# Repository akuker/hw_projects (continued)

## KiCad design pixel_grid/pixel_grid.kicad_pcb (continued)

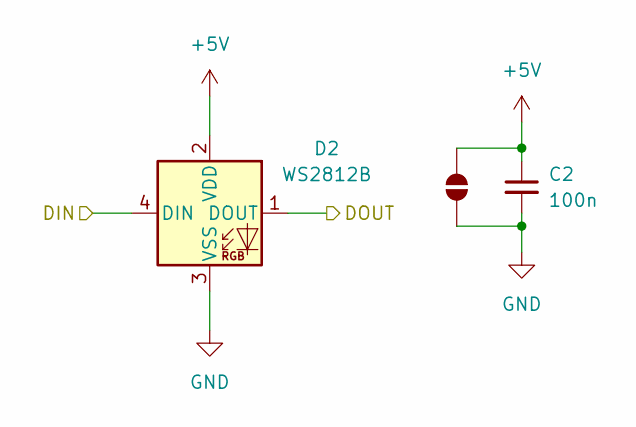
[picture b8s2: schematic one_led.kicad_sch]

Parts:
C2: 100n; C_0402_1005Metric; LCSC C1525
D2: WS2812B; LED_WS2812B-1615_1.5x1.6mm; LCSC C5349954
JP71: SolderJumper_2_Open; Pin_D0.6mm_Via

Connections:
+5V: C2.1, D2.2 (VDD), JP71.2 (B); also elsewhere on the board
/Ten_Leds/One_LED1/DOUT: D2.1 (DOUT); also elsewhere on the board
/Ten_Leds/One_LED/DOUT: D2.4 (DIN); also elsewhere on the board
GND: C2.2, D2.3 (VSS), JP71.1 (A); also elsewhere on the board

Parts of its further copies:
C1, C3, C4, C5, C6, C7, C8, C9, C10, C11, C12, C13, C14, C15, C16, C17, C18, C19, C20, C21, C22, C23, C24, C25, C26, C27, C28, C29, C30, C31, C32, C33, C34, C35, C36, C37, C38, C39, C40, C41, C42, C43, C44, C45, C46, C47, C48, C49, C50, C51, C52, C53, C54, C55, C56, C57, C58, C59, C60, C61, C62, C63, C64, C65, C66, C67, C68, C69, C70, C71, C72, C73, C74, C75, C76, C77, C78, C79, C80, C81, C82, C83, C84, C85, C86, C87, C88, C89, C90, C91, C92, C93, C94, C95, C96, C97, C98, C99, C100: 100n; C_0402_1005Metric; LCSC C1525
D1, D3, D4, D5, D6, D7, D8, D9, D10, D11, D12, D13, D14, D15, D16, D17, D18, D19, D20, D21, D22, D23, D24, D25, D26, D27, D28, D29, D30, D31, D32, D33, D34, D35, D36, D37, D38, D39, D40, D41, D42, D43, D44, D45, D46, D47, D48, D49, D50, D51, D52, D53, D54, D55, D56, D57, D58, D59, D60, D61, D62, D63, D64, D65, D66, D67, D68, D69, D70, D71, D72, D73, D74, D75, D76, D77, D78, D79, D80, D81, D82, D83, D84, D85, D86, D87, D88, D89, D90, D91, D92, D93, D94, D95, D96, D97, D98, D99, D100: WS2812B; LED_WS2812B-1615_1.5x1.6mm; LCSC C5349954
JP1, JP2, JP3, JP4, JP5, JP6, JP7, JP8, JP9, JP10, JP11, JP12, JP13, JP14, JP15, JP16, JP17, JP18, JP19, JP20, JP21, JP22, JP23, JP24, JP25, JP26, JP27, JP28, JP29, JP30, JP31, JP32, JP33, JP34, JP35, JP36, JP37, JP38, JP39, JP40, JP41, JP42, JP43, JP44, JP45, JP46, JP47, JP48, JP49, JP50, JP51, JP52, JP53, JP54, JP55, JP56, JP57, JP58, JP59, JP60, JP61, JP62, JP63, JP64, JP65, JP66, JP67, JP68, JP69, JP70, JP72, JP73, JP74, JP75, JP76, JP77, JP78, JP79, JP80, JP81, JP82, JP83, JP84, JP85, JP86, JP87, JP88, JP89, JP90, JP91, JP92, JP93, JP94, JP95, JP96, JP97, JP98, JP99, JP100: SolderJumper_2_Open; Pin_D0.6mm_Via

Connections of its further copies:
+5V: C1.1, C3.1, C4.1, C5.1, C6.1, C7.1, C8.1, C9.1, C10.1, C11.1, C12.1, C13.1, C14.1, C15.1, C16.1, C17.1, C18.1, C19.1, C20.1, C21.1, C22.1, C23.1, C24.1, C25.1, C26.1, C27.1, C28.1, C29.1, C30.1, C31.1, C32.1, C33.1, C34.1, C35.1, C36.1, C37.1, C38.1, C39.1, C40.1, C41.1, C42.1, C43.1, C44.1, C45.1, C46.1, C47.1, C48.1, C49.1, C50.1, C51.1, C52.1, C53.1, C54.1, C55.1, C56.1, C57.1, C58.1, C59.1, C60.1, C61.1, C62.1, C63.1, C64.1, C65.1, C66.1, C67.1, C68.1, C69.1, C70.1, C71.1, C72.1, C73.1, C74.1, C75.1, C76.1, C77.1, C78.1, C79.1, C80.1, C81.1, C82.1, C83.1, C84.1, C85.1, C86.1, C87.1, C88.1, C89.1, C90.1, C91.1, C92.1, C93.1, C94.1, C95.1, C96.1, C97.1, C98.1, C99.1, C100.1, D1.2 (VDD), D3.2 (VDD), D4.2 (VDD), D5.2 (VDD), D6.2 (VDD), D7.2 (VDD), D8.2 (VDD), D9.2 (VDD), D10.2 (VDD), D11.2 (VDD), D12.2 (VDD), D13.2 (VDD), D14.2 (VDD), D15.2 (VDD), D16.2 (VDD), D17.2 (VDD), D18.2 (VDD), D19.2 (VDD), D20.2 (VDD), D21.2 (VDD), D22.2 (VDD), D23.2 (VDD), D24.2 (VDD), D25.2 (VDD), D26.2 (VDD), D27.2 (VDD), D28.2 (VDD), D29.2 (VDD), D30.2 (VDD), D31.2 (VDD), D32.2 (VDD), D33.2 (VDD), D34.2 (VDD), D35.2 (VDD), D36.2 (VDD), D37.2 (VDD), D38.2 (VDD), D39.2 (VDD), D40.2 (VDD), D41.2 (VDD), D42.2 (VDD), D43.2 (VDD), D44.2 (VDD), D45.2 (VDD), D46.2 (VDD), D47.2 (VDD), D48.2 (VDD), D49.2 (VDD), D50.2 (VDD), D51.2 (VDD), D52.2 (VDD), D53.2 (VDD), D54.2 (VDD), D55.2 (VDD), D56.2 (VDD), D57.2 (VDD), D58.2 (VDD), D59.2 (VDD), D60.2 (VDD), D61.2 (VDD), D62.2 (VDD), D63.2 (VDD), D64.2 (VDD), D65.2 (VDD), D66.2 (VDD), D67.2 (VDD), D68.2 (VDD), D69.2 (VDD), D70.2 (VDD), D71.2 (VDD), D72.2 (VDD), D73.2 (VDD), D74.2 (VDD), D75.2 (VDD), D76.2 (VDD), D77.2 (VDD), D78.2 (VDD), D79.2 (VDD), D80.2 (VDD), D81.2 (VDD), D82.2 (VDD), D83.2 (VDD), D84.2 (VDD), D85.2 (VDD), D86.2 (VDD), D87.2 (VDD), D88.2 (VDD), D89.2 (VDD), D90.2 (VDD), D91.2 (VDD), D92.2 (VDD), D93.2 (VDD), D94.2 (VDD), D95.2 (VDD), D96.2 (VDD), D97.2 (VDD), D98.2 (VDD), D99.2 (VDD), D100.2 (VDD), JP1.2 (B), JP2.2 (B), JP3.2 (B), JP4.2 (B), JP5.2 (B), JP6.2 (B), JP7.2 (B), JP8.2 (B), JP9.2 (B), JP10.2 (B), JP11.2 (B), JP12.2 (B), JP13.2 (B), JP14.2 (B), JP15.2 (B), JP16.2 (B), JP17.2 (B), JP18.2 (B), JP19.2 (B), JP20.2 (B), JP21.2 (B), JP22.2 (B), JP23.2 (B), JP24.2 (B), JP25.2 (B), JP26.2 (B), JP27.2 (B), JP28.2 (B), JP29.2 (B), JP30.2 (B), JP31.2 (B), JP32.2 (B), JP33.2 (B), JP34.2 (B), JP35.2 (B), JP36.2 (B), JP37.2 (B), JP38.2 (B), JP39.2 (B), JP40.2 (B), JP41.2 (B), JP42.2 (B), JP43.2 (B), JP44.2 (B), JP45.2 (B), JP46.2 (B), JP47.2 (B), JP48.2 (B), JP49.2 (B), JP50.2 (B), JP51.2 (B), JP52.2 (B), JP53.2 (B), JP54.2 (B), JP55.2 (B), JP56.2 (B), JP57.2 (B), JP58.2 (B), JP59.2 (B), JP60.2 (B), JP61.2 (B), JP62.2 (B), JP63.2 (B), JP64.2 (B), JP65.2 (B), JP66.2 (B), JP67.2 (B), JP68.2 (B), JP69.2 (B), JP70.2 (B), JP72.2 (B), JP73.2 (B), JP74.2 (B), JP75.2 (B), JP76.2 (B), JP77.2 (B), JP78.2 (B), JP79.2 (B), JP80.2 (B), JP81.2 (B), JP82.2 (B), JP83.2 (B), JP84.2 (B), JP85.2 (B), JP86.2 (B), JP87.2 (B), JP88.2 (B), JP89.2 (B), JP90.2 (B), JP91.2 (B), JP92.2 (B), JP93.2 (B), JP94.2 (B), JP95.2 (B), JP96.2 (B), JP97.2 (B), JP98.2 (B), JP99.2 (B), JP100.2 (B); also elsewhere on the board
/Ten_Leds1/DOUT: D20.1 (DOUT), D21.4 (DIN)
/Ten_Leds1/One_LED1/DOUT: D12.1 (DOUT), D13.4 (DIN)
/Ten_Leds1/One_LED2/DOUT: D13.1 (DOUT), D14.4 (DIN)
/Ten_Leds1/One_LED3/DOUT: D14.1 (DOUT), D15.4 (DIN)
/Ten_Leds1/One_LED4/DOUT: D15.1 (DOUT), D16.4 (DIN)
/Ten_Leds1/One_LED5/DOUT: D16.1 (DOUT), D17.4 (DIN)
/Ten_Leds1/One_LED6/DOUT: D17.1 (DOUT), D18.4 (DIN)
/Ten_Leds1/One_LED7/DOUT: D18.1 (DOUT), D19.4 (DIN)
/Ten_Leds1/One_LED8/DOUT: D19.1 (DOUT), D20.4 (DIN)
/Ten_Leds1/One_LED/DOUT: D11.1 (DOUT), D12.4 (DIN)
/Ten_Leds2/DOUT: D30.1 (DOUT), D31.4 (DIN)
/Ten_Leds2/One_LED1/DOUT: D22.1 (DOUT), D23.4 (DIN)
/Ten_Leds2/One_LED2/DOUT: D23.1 (DOUT), D24.4 (DIN)
/Ten_Leds2/One_LED3/DOUT: D24.1 (DOUT), D25.4 (DIN)
/Ten_Leds2/One_LED4/DOUT: D25.1 (DOUT), D26.4 (DIN)
/Ten_Leds2/One_LED5/DOUT: D26.1 (DOUT), D27.4 (DIN)
/Ten_Leds2/One_LED6/DOUT: D27.1 (DOUT), D28.4 (DIN)
/Ten_Leds2/One_LED7/DOUT: D28.1 (DOUT), D29.4 (DIN)
/Ten_Leds2/One_LED8/DOUT: D29.1 (DOUT), D30.4 (DIN)
/Ten_Leds2/One_LED/DOUT: D21.1 (DOUT), D22.4 (DIN)
/Ten_Leds3/DOUT: D40.1 (DOUT), D41.4 (DIN)
/Ten_Leds3/One_LED1/DOUT: D32.1 (DOUT), D33.4 (DIN)
/Ten_Leds3/One_LED2/DOUT: D33.1 (DOUT), D34.4 (DIN)
/Ten_Leds3/One_LED3/DOUT: D34.1 (DOUT), D35.4 (DIN)
/Ten_Leds3/One_LED4/DOUT: D35.1 (DOUT), D36.4 (DIN)
/Ten_Leds3/One_LED5/DOUT: D36.1 (DOUT), D37.4 (DIN)
/Ten_Leds3/One_LED6/DOUT: D37.1 (DOUT), D38.4 (DIN)
/Ten_Leds3/One_LED7/DOUT: D38.1 (DOUT), D39.4 (DIN)
/Ten_Leds3/One_LED8/DOUT: D39.1 (DOUT), D40.4 (DIN)
/Ten_Leds3/One_LED/DOUT: D31.1 (DOUT), D32.4 (DIN)
/Ten_Leds4/DOUT: D50.1 (DOUT), D51.4 (DIN)
/Ten_Leds4/One_LED1/DOUT: D42.1 (DOUT), D43.4 (DIN)
/Ten_Leds4/One_LED2/DOUT: D43.1 (DOUT), D44.4 (DIN)
/Ten_Leds4/One_LED3/DOUT: D44.1 (DOUT), D45.4 (DIN)
/Ten_Leds4/One_LED4/DOUT: D45.1 (DOUT), D46.4 (DIN)
/Ten_Leds4/One_LED5/DOUT: D46.1 (DOUT), D47.4 (DIN)
/Ten_Leds4/One_LED6/DOUT: D47.1 (DOUT), D48.4 (DIN)
/Ten_Leds4/One_LED7/DOUT: D48.1 (DOUT), D49.4 (DIN)
/Ten_Leds4/One_LED8/DOUT: D49.1 (DOUT), D50.4 (DIN)
/Ten_Leds4/One_LED/DOUT: D41.1 (DOUT), D42.4 (DIN)
/Ten_Leds5/DOUT: D60.1 (DOUT), D61.4 (DIN)
/Ten_Leds5/One_LED1/DOUT: D52.1 (DOUT), D53.4 (DIN)
/Ten_Leds5/One_LED2/DOUT: D53.1 (DOUT), D54.4 (DIN)
/Ten_Leds5/One_LED3/DOUT: D54.1 (DOUT), D55.4 (DIN)
/Ten_Leds5/One_LED4/DOUT: D55.1 (DOUT), D56.4 (DIN)
/Ten_Leds5/One_LED5/DOUT: D56.1 (DOUT), D57.4 (DIN)
/Ten_Leds5/One_LED6/DOUT: D57.1 (DOUT), D58.4 (DIN)
/Ten_Leds5/One_LED7/DOUT: D58.1 (DOUT), D59.4 (DIN)
/Ten_Leds5/One_LED8/DOUT: D59.1 (DOUT), D60.4 (DIN)
/Ten_Leds5/One_LED/DOUT: D51.1 (DOUT), D52.4 (DIN)
/Ten_Leds6/DOUT: D70.1 (DOUT), D71.4 (DIN)
/Ten_Leds6/One_LED1/DOUT: D62.1 (DOUT), D63.4 (DIN)
/Ten_Leds6/One_LED2/DOUT: D63.1 (DOUT), D64.4 (DIN)
/Ten_Leds6/One_LED3/DOUT: D64.1 (DOUT), D65.4 (DIN)
/Ten_Leds6/One_LED4/DOUT: D65.1 (DOUT), D66.4 (DIN)
/Ten_Leds6/One_LED5/DOUT: D66.1 (DOUT), D67.4 (DIN)
/Ten_Leds6/One_LED6/DOUT: D67.1 (DOUT), D68.4 (DIN)
/Ten_Leds6/One_LED7/DOUT: D68.1 (DOUT), D69.4 (DIN)
/Ten_Leds6/One_LED8/DOUT: D69.1 (DOUT), D70.4 (DIN)
/Ten_Leds6/One_LED/DOUT: D61.1 (DOUT), D62.4 (DIN)
/Ten_Leds7/DOUT: D80.1 (DOUT), D81.4 (DIN)
/Ten_Leds7/One_LED1/DOUT: D72.1 (DOUT), D73.4 (DIN)
/Ten_Leds7/One_LED2/DOUT: D73.1 (DOUT), D74.4 (DIN)
/Ten_Leds7/One_LED3/DOUT: D74.1 (DOUT), D75.4 (DIN)
/Ten_Leds7/One_LED4/DOUT: D75.1 (DOUT), D76.4 (DIN)
/Ten_Leds7/One_LED5/DOUT: D76.1 (DOUT), D77.4 (DIN)
/Ten_Leds7/One_LED6/DOUT: D77.1 (DOUT), D78.4 (DIN)
/Ten_Leds7/One_LED7/DOUT: D78.1 (DOUT), D79.4 (DIN)
/Ten_Leds7/One_LED8/DOUT: D79.1 (DOUT), D80.4 (DIN)
/Ten_Leds7/One_LED/DOUT: D71.1 (DOUT), D72.4 (DIN)
/Ten_Leds8/DOUT: D90.1 (DOUT), D91.4 (DIN)
/Ten_Leds8/One_LED1/DOUT: D82.1 (DOUT), D83.4 (DIN)
/Ten_Leds8/One_LED2/DOUT: D83.1 (DOUT), D84.4 (DIN)
/Ten_Leds8/One_LED3/DOUT: D84.1 (DOUT), D85.4 (DIN)
/Ten_Leds8/One_LED4/DOUT: D85.1 (DOUT), D86.4 (DIN)
/Ten_Leds8/One_LED5/DOUT: D86.1 (DOUT), D87.4 (DIN)
/Ten_Leds8/One_LED6/DOUT: D87.1 (DOUT), D88.4 (DIN)
/Ten_Leds8/One_LED7/DOUT: D88.1 (DOUT), D89.4 (DIN)
/Ten_Leds8/One_LED8/DOUT: D89.1 (DOUT), D90.4 (DIN)
/Ten_Leds8/One_LED/DOUT: D81.1 (DOUT), D82.4 (DIN)
/Ten_Leds9/One_LED1/DOUT: D92.1 (DOUT), D93.4 (DIN)
/Ten_Leds9/One_LED2/DOUT: D93.1 (DOUT), D94.4 (DIN)
/Ten_Leds9/One_LED3/DOUT: D94.1 (DOUT), D95.4 (DIN)
/Ten_Leds9/One_LED4/DOUT: D95.1 (DOUT), D96.4 (DIN)
/Ten_Leds9/One_LED5/DOUT: D96.1 (DOUT), D97.4 (DIN)
/Ten_Leds9/One_LED6/DOUT: D97.1 (DOUT), D98.4 (DIN)
/Ten_Leds9/One_LED7/DOUT: D98.1 (DOUT), D99.4 (DIN)
/Ten_Leds9/One_LED8/DOUT: D99.1 (DOUT), D100.4 (DIN)
/Ten_Leds9/One_LED/DOUT: D91.1 (DOUT), D92.4 (DIN)
/Ten_Leds/DOUT: D10.1 (DOUT), D11.4 (DIN)
/Ten_Leds/One_LED1/DOUT: D3.4 (DIN); also elsewhere on the board
/Ten_Leds/One_LED2/DOUT: D3.1 (DOUT), D4.4 (DIN)
/Ten_Leds/One_LED3/DOUT: D4.1 (DOUT), D5.4 (DIN)
/Ten_Leds/One_LED4/DOUT: D5.1 (DOUT), D6.4 (DIN)
/Ten_Leds/One_LED5/DOUT: D6.1 (DOUT), D7.4 (DIN)
/Ten_Leds/One_LED6/DOUT: D7.1 (DOUT), D8.4 (DIN)
/Ten_Leds/One_LED7/DOUT: D8.1 (DOUT), D9.4 (DIN)
/Ten_Leds/One_LED8/DOUT: D9.1 (DOUT), D10.4 (DIN)
/Ten_Leds/One_LED/DOUT: D1.1 (DOUT); also elsewhere on the board
DIN: D1.4 (DIN); also elsewhere on the board
DOUT: D100.1 (DOUT); also elsewhere on the board
GND: C1.2, C3.2, C4.2, C5.2, C6.2, C7.2, C8.2, C9.2, C10.2, C11.2, C12.2, C13.2, C14.2, C15.2, C16.2, C17.2, C18.2, C19.2, C20.2, C21.2, C22.2, C23.2, C24.2, C25.2, C26.2, C27.2, C28.2, C29.2, C30.2, C31.2, C32.2, C33.2, C34.2, C35.2, C36.2, C37.2, C38.2, C39.2, C40.2, C41.2, C42.2, C43.2, C44.2, C45.2, C46.2, C47.2, C48.2, C49.2, C50.2, C51.2, C52.2, C53.2, C54.2, C55.2, C56.2, C57.2, C58.2, C59.2, C60.2, C61.2, C62.2, C63.2, C64.2, C65.2, C66.2, C67.2, C68.2, C69.2, C70.2, C71.2, C72.2, C73.2, C74.2, C75.2, C76.2, C77.2, C78.2, C79.2, C80.2, C81.2, C82.2, C83.2, C84.2, C85.2, C86.2, C87.2, C88.2, C89.2, C90.2, C91.2, C92.2, C93.2, C94.2, C95.2, C96.2, C97.2, C98.2, C99.2, C100.2, D1.3 (VSS), D3.3 (VSS), D4.3 (VSS), D5.3 (VSS), D6.3 (VSS), D7.3 (VSS), D8.3 (VSS), D9.3 (VSS), D10.3 (VSS), D11.3 (VSS), D12.3 (VSS), D13.3 (VSS), D14.3 (VSS), D15.3 (VSS), D16.3 (VSS), D17.3 (VSS), D18.3 (VSS), D19.3 (VSS), D20.3 (VSS), D21.3 (VSS), D22.3 (VSS), D23.3 (VSS), D24.3 (VSS), D25.3 (VSS), D26.3 (VSS), D27.3 (VSS), D28.3 (VSS), D29.3 (VSS), D30.3 (VSS), D31.3 (VSS), D32.3 (VSS), D33.3 (VSS), D34.3 (VSS), D35.3 (VSS), D36.3 (VSS), D37.3 (VSS), D38.3 (VSS), D39.3 (VSS), D40.3 (VSS), D41.3 (VSS), D42.3 (VSS), D43.3 (VSS), D44.3 (VSS), D45.3 (VSS), D46.3 (VSS), D47.3 (VSS), D48.3 (VSS), D49.3 (VSS), D50.3 (VSS), D51.3 (VSS), D52.3 (VSS), D53.3 (VSS), D54.3 (VSS), D55.3 (VSS), D56.3 (VSS), D57.3 (VSS), D58.3 (VSS), D59.3 (VSS), D60.3 (VSS), D61.3 (VSS), D62.3 (VSS), D63.3 (VSS), D64.3 (VSS), D65.3 (VSS), D66.3 (VSS), D67.3 (VSS), D68.3 (VSS), D69.3 (VSS), D70.3 (VSS), D71.3 (VSS), D72.3 (VSS), D73.3 (VSS), D74.3 (VSS), D75.3 (VSS), D76.3 (VSS), D77.3 (VSS), D78.3 (VSS), D79.3 (VSS), D80.3 (VSS), D81.3 (VSS), D82.3 (VSS), D83.3 (VSS), D84.3 (VSS), D85.3 (VSS), D86.3 (VSS), D87.3 (VSS), D88.3 (VSS), D89.3 (VSS), D90.3 (VSS), D91.3 (VSS), D92.3 (VSS), D93.3 (VSS), D94.3 (VSS), D95.3 (VSS), D96.3 (VSS), D97.3 (VSS), D98.3 (VSS), D99.3 (VSS), D100.3 (VSS), JP1.1 (A), JP2.1 (A), JP3.1 (A), JP4.1 (A), JP5.1 (A), JP6.1 (A), JP7.1 (A), JP8.1 (A), JP9.1 (A), JP10.1 (A), JP11.1 (A), JP12.1 (A), JP13.1 (A), JP14.1 (A), JP15.1 (A), JP16.1 (A), JP17.1 (A), JP18.1 (A), JP19.1 (A), JP20.1 (A), JP21.1 (A), JP22.1 (A), JP23.1 (A), JP24.1 (A), JP25.1 (A), JP26.1 (A), JP27.1 (A), JP28.1 (A), JP29.1 (A), JP30.1 (A), JP31.1 (A), JP32.1 (A), JP33.1 (A), JP34.1 (A), JP35.1 (A), JP36.1 (A), JP37.1 (A), JP38.1 (A), JP39.1 (A), JP40.1 (A), JP41.1 (A), JP42.1 (A), JP43.1 (A), JP44.1 (A), JP45.1 (A), JP46.1 (A), JP47.1 (A), JP48.1 (A), JP49.1 (A), JP50.1 (A), JP51.1 (A), JP52.1 (A), JP53.1 (A), JP54.1 (A), JP55.1 (A), JP56.1 (A), JP57.1 (A), JP58.1 (A), JP59.1 (A), JP60.1 (A), JP61.1 (A), JP62.1 (A), JP63.1 (A), JP64.1 (A), JP65.1 (A), JP66.1 (A), JP67.1 (A), JP68.1 (A), JP69.1 (A), JP70.1 (A), JP72.1 (A), JP73.1 (A), JP74.1 (A), JP75.1 (A), JP76.1 (A), JP77.1 (A), JP78.1 (A), JP79.1 (A), JP80.1 (A), JP81.1 (A), JP82.1 (A), JP83.1 (A), JP84.1 (A), JP85.1 (A), JP86.1 (A), JP87.1 (A), JP88.1 (A), JP89.1 (A), JP90.1 (A), JP91.1 (A), JP92.1 (A), JP93.1 (A), JP94.1 (A), JP95.1 (A), JP96.1 (A), JP97.1 (A), JP98.1 (A), JP99.1 (A), JP100.1 (A); also elsewhere on the board

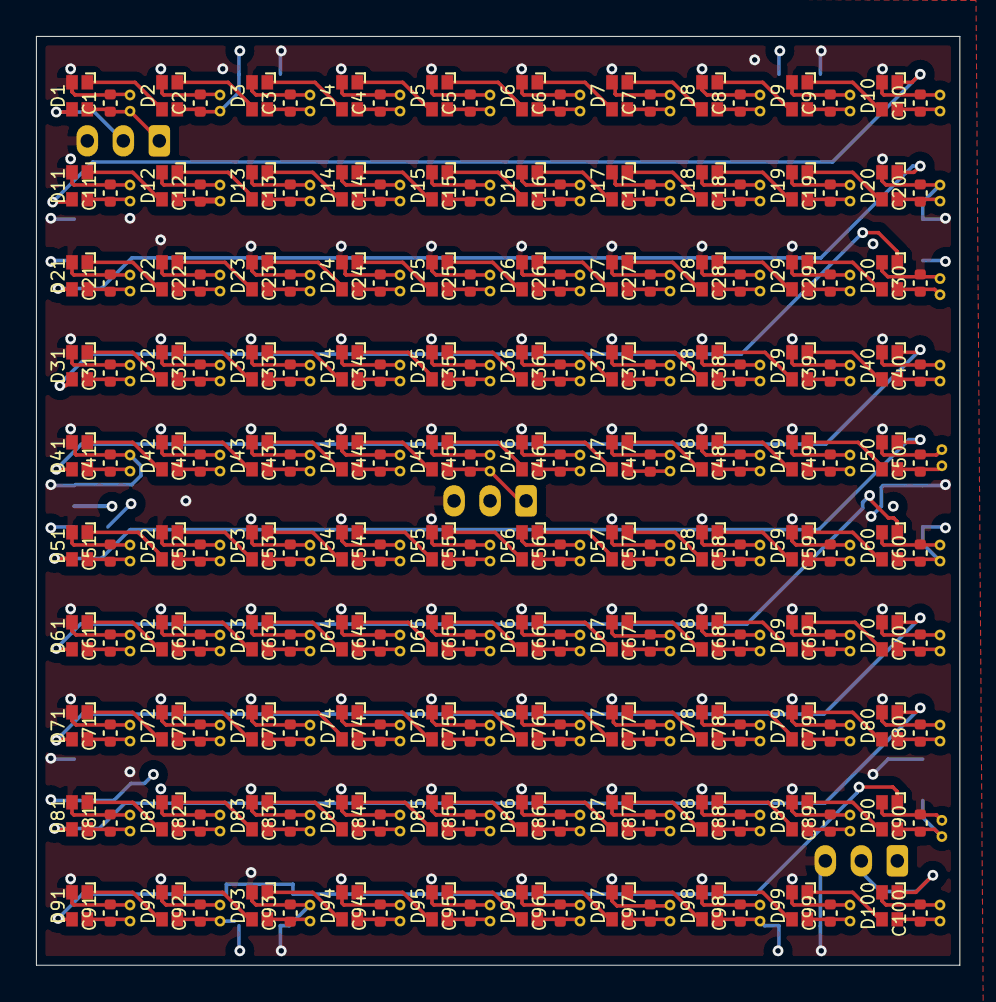
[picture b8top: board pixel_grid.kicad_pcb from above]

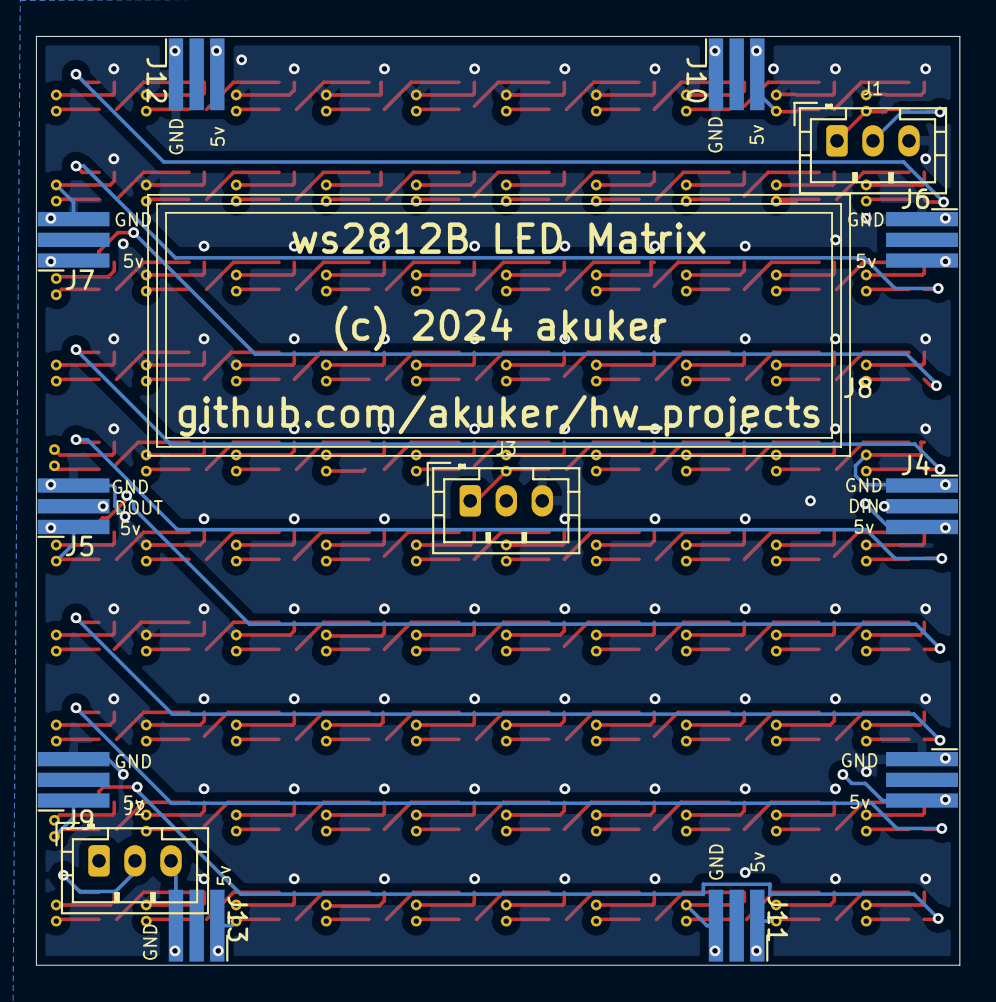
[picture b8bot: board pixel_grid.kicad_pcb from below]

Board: 4 copper layers, 51.3 x 51.6 mm, 313 parts (13 on the bottom side), 103 nets.

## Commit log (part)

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2021-02-08 First draft of super simple raspberry pi fan hat
2021-02-10 First draft
2021-02-10 Added ADB and Teensy
2021-03-20 Updated for version 1.0
2021-03-21 Apple II breakout board
2021-03-21 Finished up Apple II breakout
2021-03-23 First draft of analog discovery 2 adapter
2021-03-24 Version 1.0
2021-05-16 40 pin breakout
2021-10-25 Bracket to hold 4ch mixer
2022-02-06 pi to Micromod ATP Carrier board adapter
2022-03-19 enclosure for filament box
2022-04-16 Updates with side panel
2022-04-16 Restore the scsi blinky lights board from RaSCSI repo
2022-04-16 rpi board with simple leds
2022-04-17 updated silkscreen
2022-04-17 generated production files
2022-04-17 Ignore kicad backup folders
2022-04-17 removed backup file
2022-04-18 Incomplete First draft
2022-04-19 Updated part numbers
2022-04-26 Added bottom lip
2022-04-26 Started updating to SMT
2022-05-04 Added simple buck converter
2022-05-04 add sumbol and library tables
2022-05-06 first draft voltage regulator
2022-05-06 added 3d model
2022-05-06 wallbrace for 3d printer
2022-05-06 Updated layout
2022-05-06 rename file
2022-05-06 rename folder
2022-05-09 As ordered v0.9
2022-06-03 ordered hdd carrier board
2022-06-03 initial placement
2022-06-03 added model for reset button
2022-06-03 as-ordered boards
2022-06-03 as ordered
2022-06-03 updated symbol table
2022-06-03 restore values
2022-06-03 fix library reference
2022-07-20 tardis pcb
2022-08-23 First draft of G3 Wallstreet WSD
2022-08-28 update 7ish
2022-12-15 working
2022-12-16 layout draft
2022-12-17 graphics updates
2023-01-02 Fan cover and control panel
2023-01-07 as ordered... I think
2023-01-07 as ordered... i think?
2023-01-07 Pico controller code
2023-03-14 first cut
2023-03-14 started layout
2023-03-15 routing complete
2023-04-12 PATA IDE Adapter Board
2023-04-12 Add pictures
2023-04-12 move incomplete projects
2023-04-12 purge old junk
2023-09-16 Initial draft of case
2023-09-18 v2b updates
2023-09-21 v1 case for sharp x68000 gamepad adapter
2023-10-14 intermediate
2023-11-19 Try 4
2023-11-29 roll holder
2023-12-19 added more holes
2023-12-30 v2 created
2024-02-17 echo show mount
2024-05-09 as-ordered host tester v1
2024-06-25 commit junk
2024-09-16 pin header breakout
2024-10-06 h89 gotek mount
2024-11-18 inline switch box
2024-12-19 as-ordered blinken lights
2025-04-28 initial draft
2025-05-01 start layout
2025-05-01 remove junk
2025-05-11 started routing
